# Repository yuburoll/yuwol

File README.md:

# yuwol
row staggered 60% hotswappable keyboard with reversible PCB, little ergo boost of [ilwol](https://github.com/yuburoll/ilwol)

The name yuwol is June in Korean.

This keyboard has additional Y/H/B keys which positioned between keyboards, and auxilary row at left outside. You may put the keycaps from numpad.

This keyboard has hotswap-only PCB.

yuwol can change layout to followings:

- Split left shift, to ISO shaped one.(2.25u to 1.25u/1u)

- Split right shift, to HHKB inspired shape.(2.75u to 1.75u/1u)

- Split outside thumb keys(2u to 1u/1u)

- Split backspace(2u to 1u/1u)

- Can use stepped caps lock

## Preparation

common:

- 2x yuwol PCB Boards, provided from the repo

- 1x printed case sets, 2 parts total, provided from the repo

- 1x 1.5-1.6T keyboard plate sets, 2 parts total, provided from the repo

- 80x diodes, normally 1N4148

- 84x Kailh hotswap sockets (or compatibles)

- 2x 4x4x1.5mm surface mount tact switches (optional, for dev boards without reset button)

- 1-6x PCB Mounted 2u Keyboard Stabilizers, normally 6

- 73-78x MX Keyswitches, normally 73

- 8x 10mm bumpon stickers

- A set of Keycaps, Full-size layout, ANSI preferred.

for wired build:

- 2x pro micro form factor dev board

- 2x USB-C 6 pin jack, top mount

- 1x USB-C data cable

- 10x M2x6 screws / or M2x3x3 heat inserts and M2x6 bolts

for wireless build:

- 2x pro micro form factor dev board, with wireless chipset

- 2x 523450 battery, with molex picoblade 1.25mm pitch male, 2pin

- 2x molex picoblade 1.25mm pitch female, 2pin

- 2x SS-12D00 switches

- 2x battery cover, provided from the repo

- 14x M2x6 screws / or M2x3x3 heat inserts and M2x6 bolts

dongle:

- 1x pro micro form factor dev board, with wireless chipset

- 1x printed dongle case sets, 2 parts total, provided from the repo

- 2x M2x6 screws / or M2x3x3 heat inserts and M2x6 bolts

- 3x 10mm bumpon stickers

## Differences between case variations

- Screw: 1.5 pi mounting holes for screws

- Insert: 3 pi mounting holes for heat inserts

## Build Guides and Miscellaneous

[yuwol Build Guide](docs/buildGuide.md)

there's some notices before the build:

- You may solder all hotswaps before soldering the dev board.

- Assemble dev board with 2.5mm height pin headers on back side, assume that components side are faced up.

- Jump a jumper when it is left hand board.

[Additional Tenting Stand](https://github.com/yuburoll/yubuGadgets/tree/main/phalilwolTentingStand)

## Licenses

all codes follow MIT license.

all designs and the hardware board follow CC BY-SA 4.0 license.

Markdown documents and photos in docs/images folder are copyrighted, all rights reserved. You can use it for [fair use](https://www.copyright.gov/fair-use/).

If you want to make a commercial product, it would be appreciated if you sponsor some bucks for me.

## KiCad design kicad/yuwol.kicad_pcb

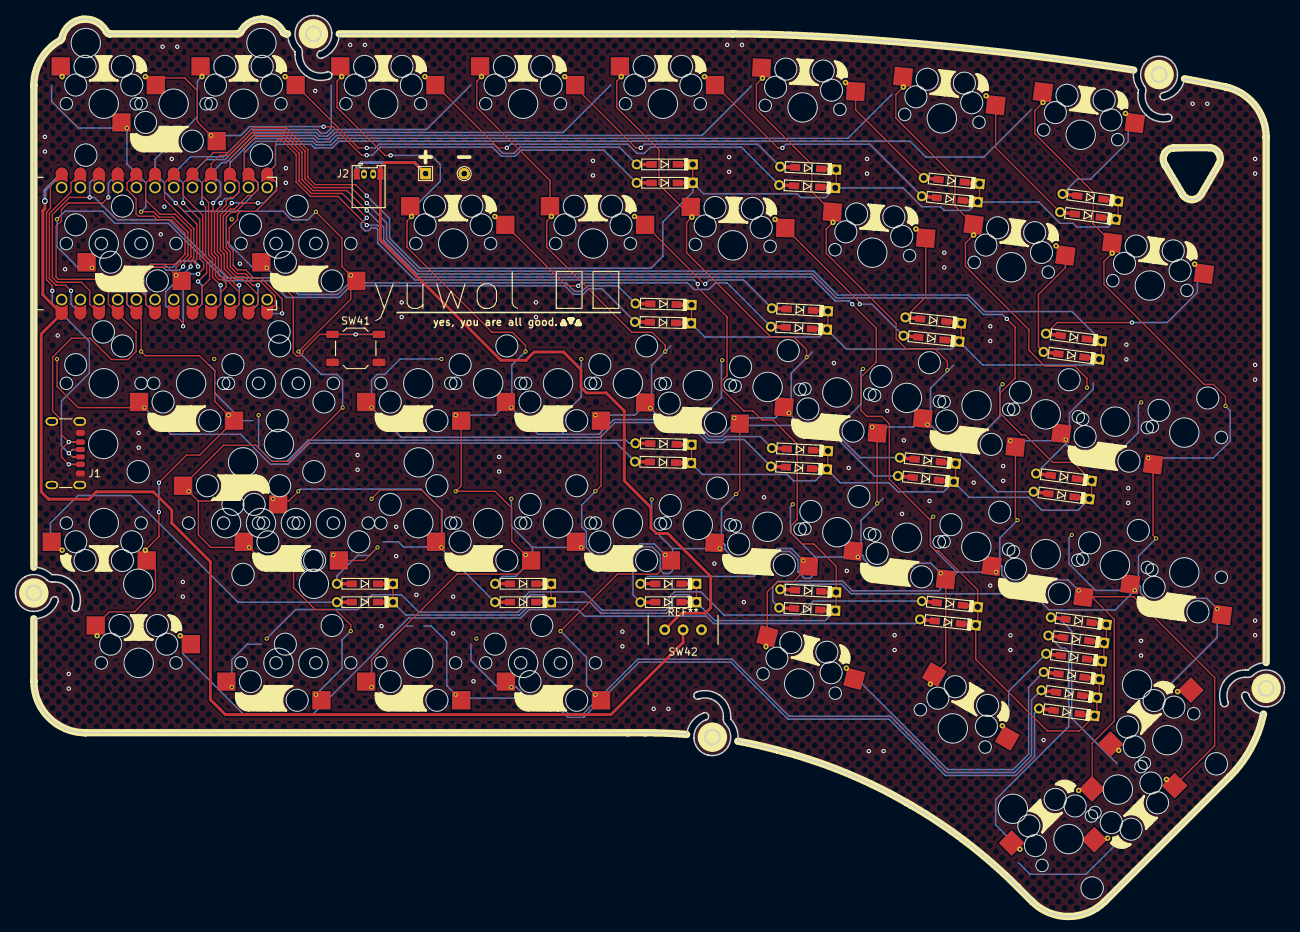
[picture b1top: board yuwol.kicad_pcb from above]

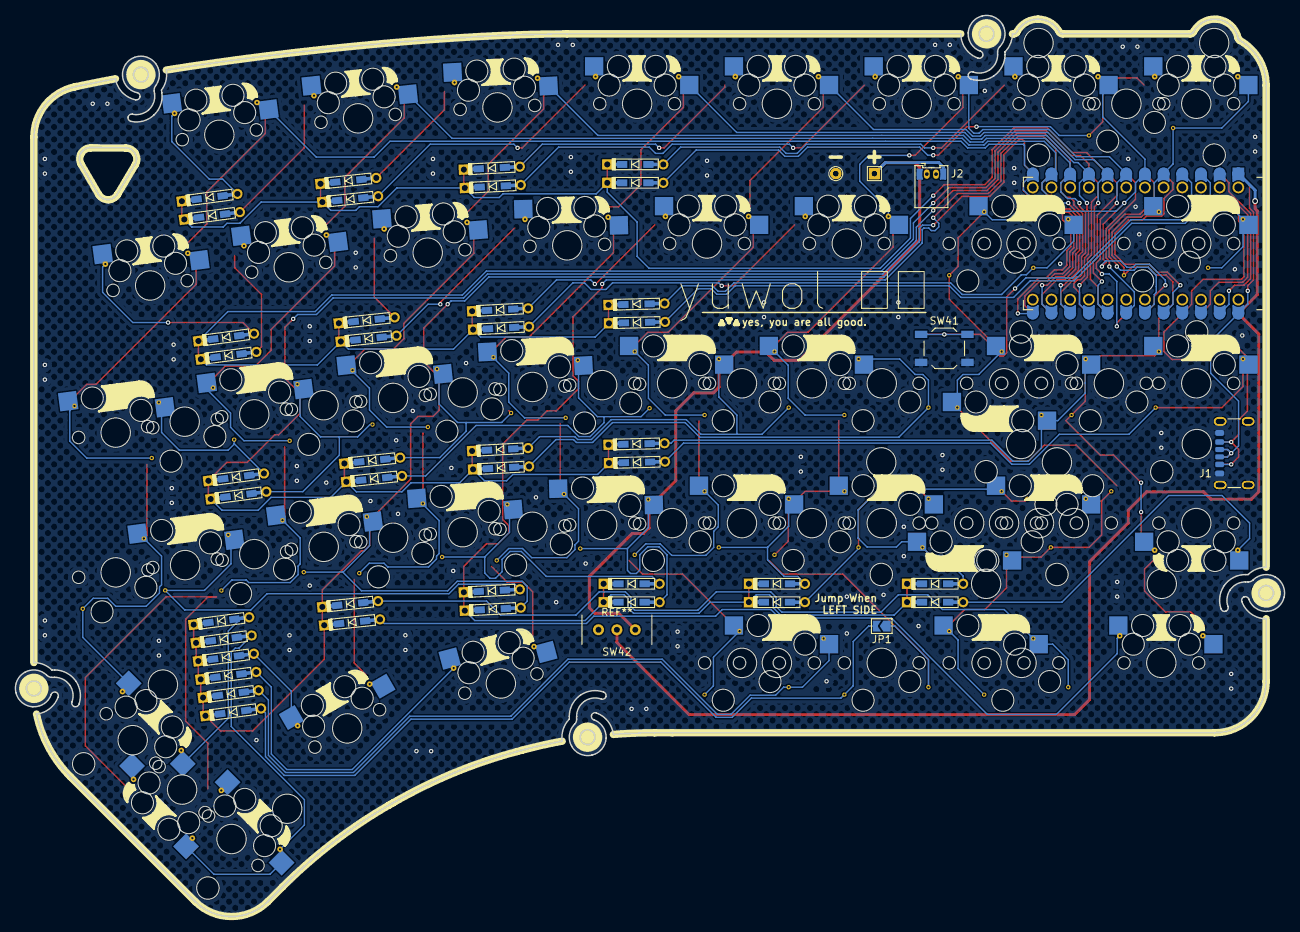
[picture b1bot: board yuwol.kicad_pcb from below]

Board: 2 copper layers, 172.5 x 122.5 mm, 115 parts (26 on the bottom side), 59 nets.

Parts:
D1, D2, D3, D4, D5, D6, D7, D8, D9, D10, D11, D12, D13, D14, D15, D16, D17, D18, D19, D20, D21, D22, D23, D24, D25, D26, D27, D28, D29, D30, D31, D32, D33, D34, D35, D36, D37, D38, D39, D40: D; Diode_TH_SMD_REVERSIBLE
J1, J1#2: USB_C_Receptacle_PowerOnly_6P; USB_C_Receptacle_GCT_USB4125-xx-x_6P_TopMnt_Horizontal
J2: Conn_01x02_Socket; Molex_PicoBlade_53048-0210_1x02_P1.25mm_Horizontal_Reversib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
JP1: SolderJumper_2_Open; SolderJumper-2_P1.3mm_Open_TrianglePad1.0x1.5mm
SW1, SW2, SW3, SW4, SW5, SW6, SW7, SW8, SW11, SW12, SW13, SW14, SW15, SW16, SW25, SW33, SW37, SW38, SW39: SW_Push; MX_Hotswap_FootprintPropertyFix_Guided
SW1#2, SW18#2, SW26, SW26#4: SW_Push; MX_HotswapOnesideReverse_Via_Guided
SW9, SW9#2, SW10, SW10#2, SW17, SW17#2, SW18, SW19, SW19#2, SW20, SW20#2, SW21, SW21#2, SW22, SW22#2, SW23, SW23#2, SW24, SW24#2, SW26#2, SW26#3, SW27, SW27#2, SW28, SW28#2, SW29, SW29#2, SW30, SW30#2, SW31, SW31#2, SW32, SW32#2, SW34, SW34#2, SW35, SW36, SW36#2: SW_Push; MX_HotswapOneside_Via_Guided
SW39#2, SW40: SW_Push; MX_HotswapReverse_FootprintPropertyFix_Guided
SW41, SW41#2: SW_Push; SW_SPST_TL3342
SW42: SW_SPDT; SW_SPDT_SS-12D00
TP+1, TP+1#2: TestPoint; TestPoint_THTPad_1.5x1.5mm_Drill0.7mm
TP-1, TP-1#2: TestPoint; TestPoint_THTPad_D1.5mm_Drill0.7mm
U1: ProMicro; ProMicro_ReveribleThru_ComponentUp_OuterPad

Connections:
BATT: J2.1, SW42.3 (C), TP+1.1 (1_1), TP+1#2.1
COL1: SW1.1, SW1#2.1, SW9.1, SW9#2.1, SW17.1, SW17#2.1, SW25.1, SW33.1, U1.20 (F4/A3)
COL2: SW2.1, SW10.1, SW10#2.1, SW18.1, SW18#2.1, SW26.1, SW26#2.1, SW26#3.1, SW26#4.1, SW34.1, SW34#2.1, U1.19 (F5/A2)
COL3: JP1.1 (A), SW3.1, SW11.1, SW19.1, SW19#2.1, SW27.1, SW27#2.1, SW35.2, U1.18 (F6/A1)
COL4: SW4.1, SW12.1, SW20.1, SW20#2.1, SW28.1, SW28#2.1, SW36.1, SW36#2.1, U1.17 (F7/A0)
COL5: SW5.1, SW13.1, SW21.1, SW21#2.1, SW29.1, SW29#2.1, SW37.1, U1.16 (B1/15)
COL6: SW6.1, SW14.1, SW22.1, SW22#2.1, SW30.1, SW30#2.1, SW38.1, U1.15 (B3/14)
COL7: SW7.1, SW15.1, SW23.1, SW23#2.1, SW31.1, SW31#2.1, SW39.1, SW39#2.1, U1.14 (B2/16)
COL8: SW8.1, SW16.1, SW24.1, SW24#2.1, SW32.1, SW32#2.1, SW40.1, U1.13 (B6/10)
GND: J1.A12 (GND), J1.B12 (GND), J1.SH (SHIELD), J1#2.A12, J1#2.B12, J1#2.SH, J2.2, SW41.2, SW41#2.2, TP-1.1 (1_1), TP-1#2.1, U1.3 (GND), U1.4 (GND), U1.23 (GND)
unnamed: D1.2 (A), SW1.2, SW1#2.2
unnamed: D2.2 (A), SW2.2
unnamed: D3.2 (A), SW3.2
unnamed: D4.2 (A), SW4.2
unnamed: D5.2 (A), SW5.2
unnamed: D6.2 (A), SW6.2
unnamed: D7.2 (A), SW7.2
unnamed: D8.2 (A), SW8.2
unnamed: D9.2 (A), SW9.2, SW9#2.2
unnamed: D10.2 (A), SW10.2, SW10#2.2
unnamed: D11.2 (A), SW11.2
unnamed: D12.2 (A), SW12.2
unnamed: D13.2 (A), SW13.2
unnamed: D14.2 (A), SW14.2
unnamed: D15.2 (A), SW15.2
unnamed: D16.2 (A), SW16.2
unnamed: D17.2 (A), SW17.2, SW17#2.2
unnamed: D18.2 (A), SW18.2, SW18#2.2
unnamed: D19.2 (A), SW19.2, SW19#2.2
unnamed: D20.2 (A), SW20.2, SW20#2.2
unnamed: D21.2 (A), SW21.2, SW21#2.2
unnamed: D22.2 (A), SW22.2, SW22#2.2
unnamed: D23.2 (A), SW23.2, SW23#2.2
unnamed: D24.2 (A), SW24.2, SW24#2.2
unnamed: D25.2 (A), SW25.2
unnamed: D26.2 (A), SW26.2, SW26#2.2, SW26#3.2, SW26#4.2
unnamed: D27.2 (A), SW27.2, SW27#2.2
unnamed: D28.2 (A), SW28.2, SW28#2.2
unnamed: D29.2 (A), SW29.2, SW29#2.2
unnamed: D30.2 (A), SW30.2, SW30#2.2
unnamed: D31.2 (A), SW31.2, SW31#2.2
unnamed: D32.2 (A), SW32.2, SW32#2.2
unnamed: D33.2 (A), SW33.2
unnamed: D34.2 (A), SW34.2, SW34#2.2
unnamed: D35.2 (A), JP1.2 (B), SW35.1
unnamed: D36.2 (A), SW36.2, SW36#2.2
unnamed: D37.2 (A), SW37.2
unnamed: D38.2 (A), SW38.2
unnamed: D39.2 (A), SW39.2, SW39#2.2
unnamed: D40.2 (A), SW40.2
RAW: SW42.2 (B), U1.24 (RAW)
ROW1: D1.1 (K), D2.1 (K), D3.1 (K), D4.1 (K), D5.1 (K), D6.1 (K), D7.1 (K), D8.1 (K), U1.8 (5/C6)
ROW2: D9.1 (K), D10.1 (K), D11.1 (K), D12.1 (K), D13.1 (K), D14.1 (K), D15.1 (K), D16.1 (K), U1.9 (6/D7)
ROW3: D17.1 (K), D18.1 (K), D19.1 (K), D20.1 (K), D21.1 (K), D22.1 (K), D23.1 (K), D24.1 (K), U1.10 (7/E6)
ROW4: D25.1 (K), D26.1 (K), D27.1 (K), D28.1 (K), D29.1 (K), D30.1 (K), D31.1 (K), D32.1 (K), U1.11 (8/B4)
ROW5: D33.1 (K), D34.1 (K), D35.1 (K), D36.1 (K), D37.1 (K), D38.1 (K), D39.1 (K), D40.1 (K), U1.12 (9/B5)
RST: SW41.1, SW41#2.1, U1.22 (RST)
SERIAL: J1.A5 (CC1), J1.B5 (CC2), J1#2.A5, J1#2.B5, U1.1 (TX0/D3)
VCC: J1.A9 (VBUS), J1.B9 (VBUS), J1#2.A9, J1#2.B9, U1.21 (VCC)
